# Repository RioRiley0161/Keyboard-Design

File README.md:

# Keyboard-Design
Custom keyboard design 
NEW FILES WONT UPLOAD SO I CREATED A NEW REVISED 60% FOR MY BASE 
----------------------------
Check out updated version at https://github.com/RioRiley0161/Keyboard-PCB

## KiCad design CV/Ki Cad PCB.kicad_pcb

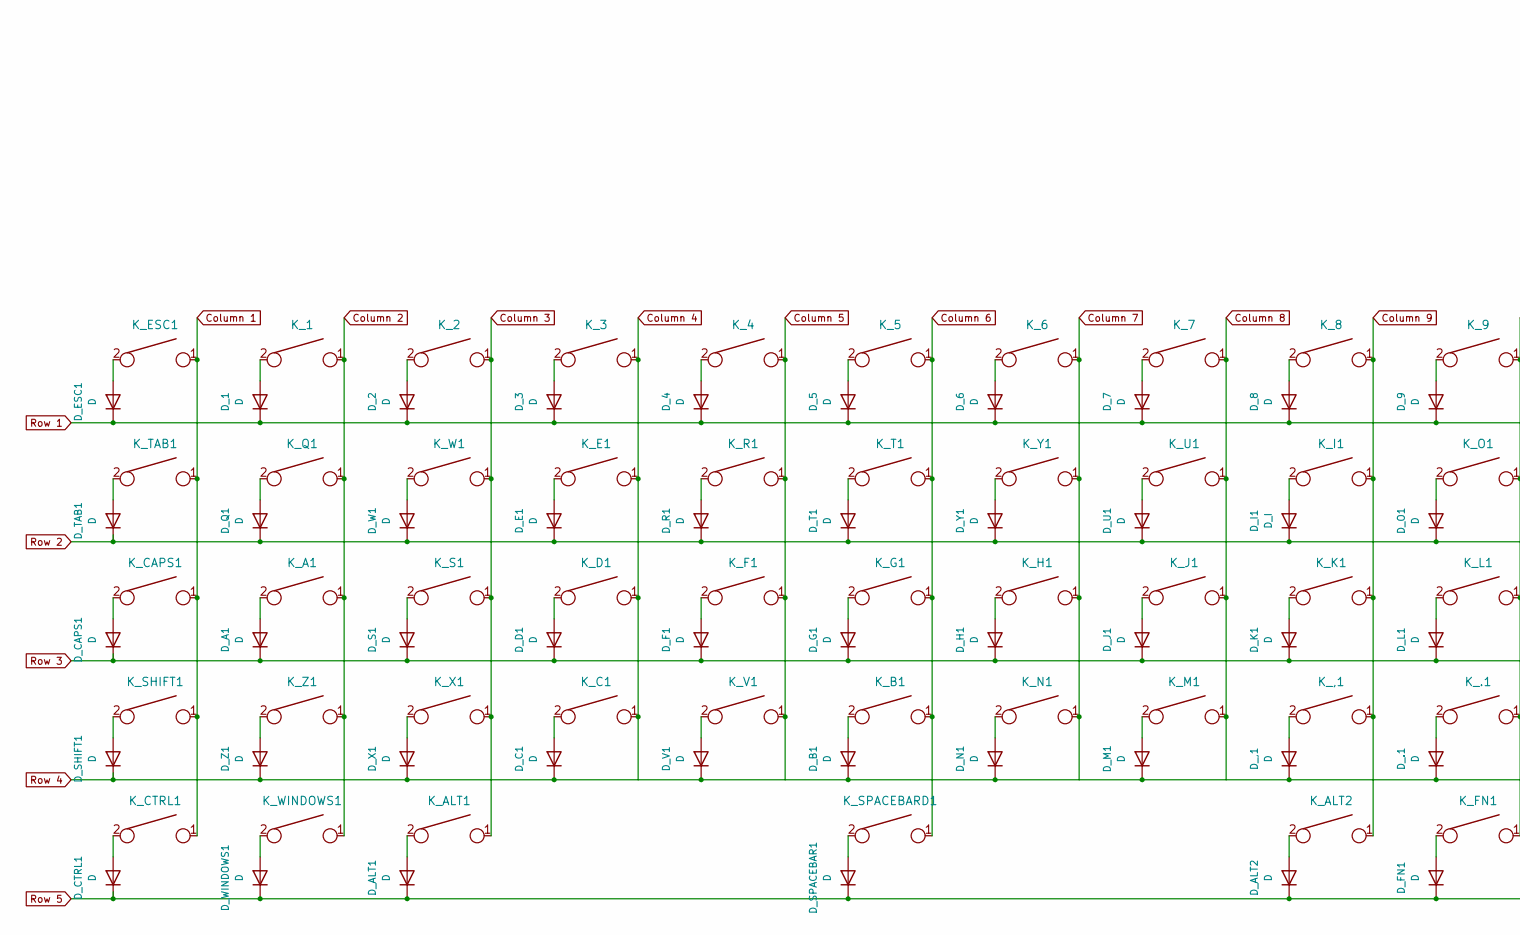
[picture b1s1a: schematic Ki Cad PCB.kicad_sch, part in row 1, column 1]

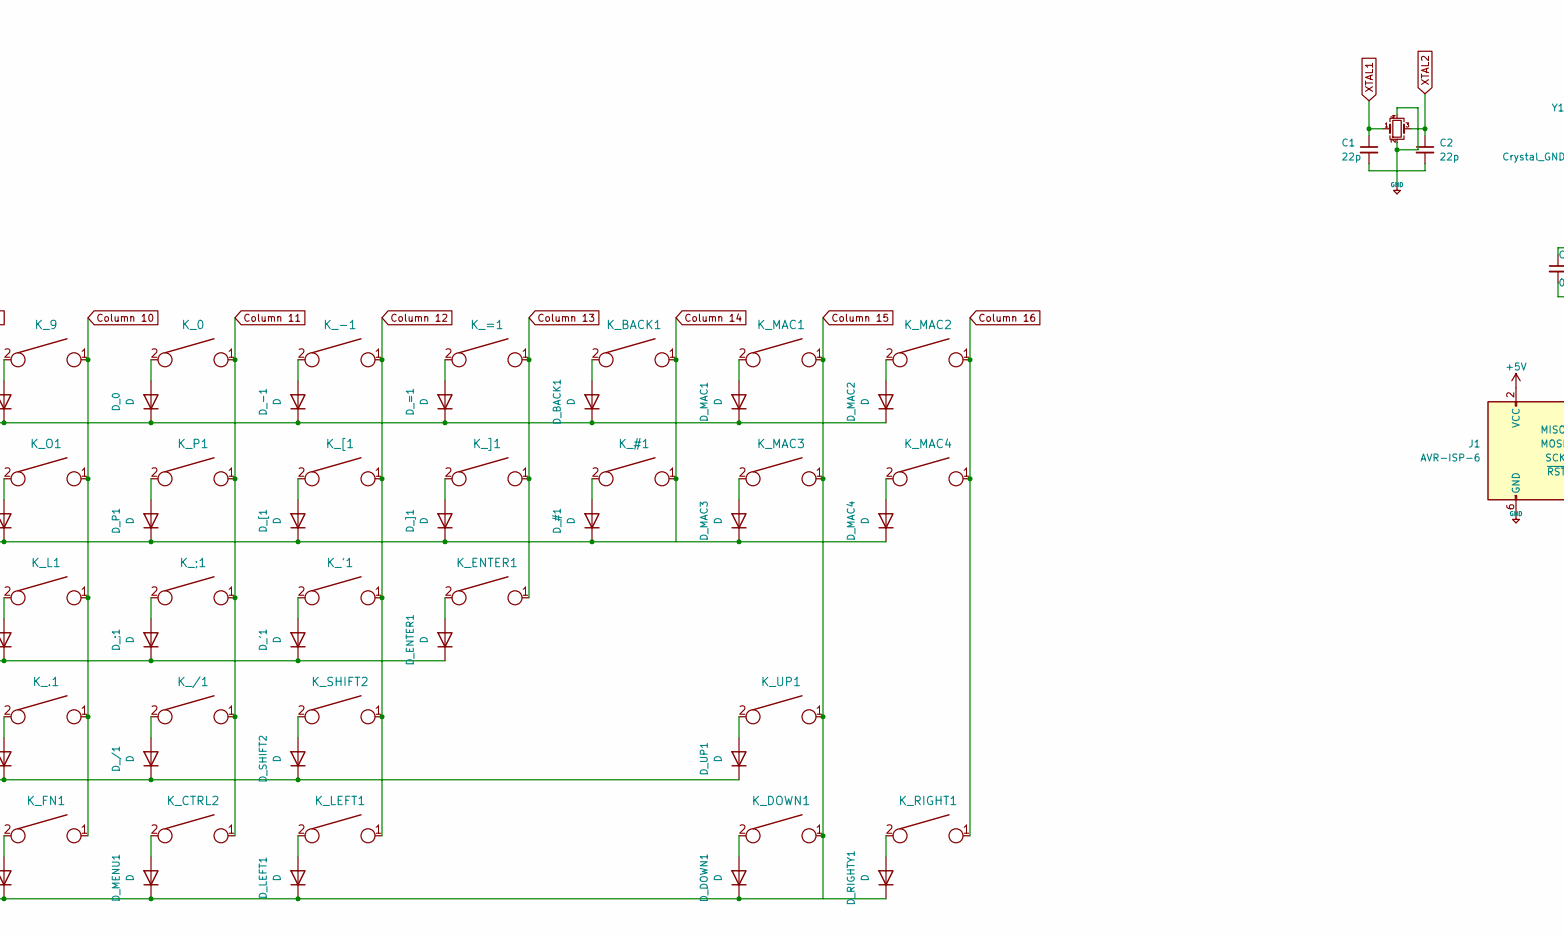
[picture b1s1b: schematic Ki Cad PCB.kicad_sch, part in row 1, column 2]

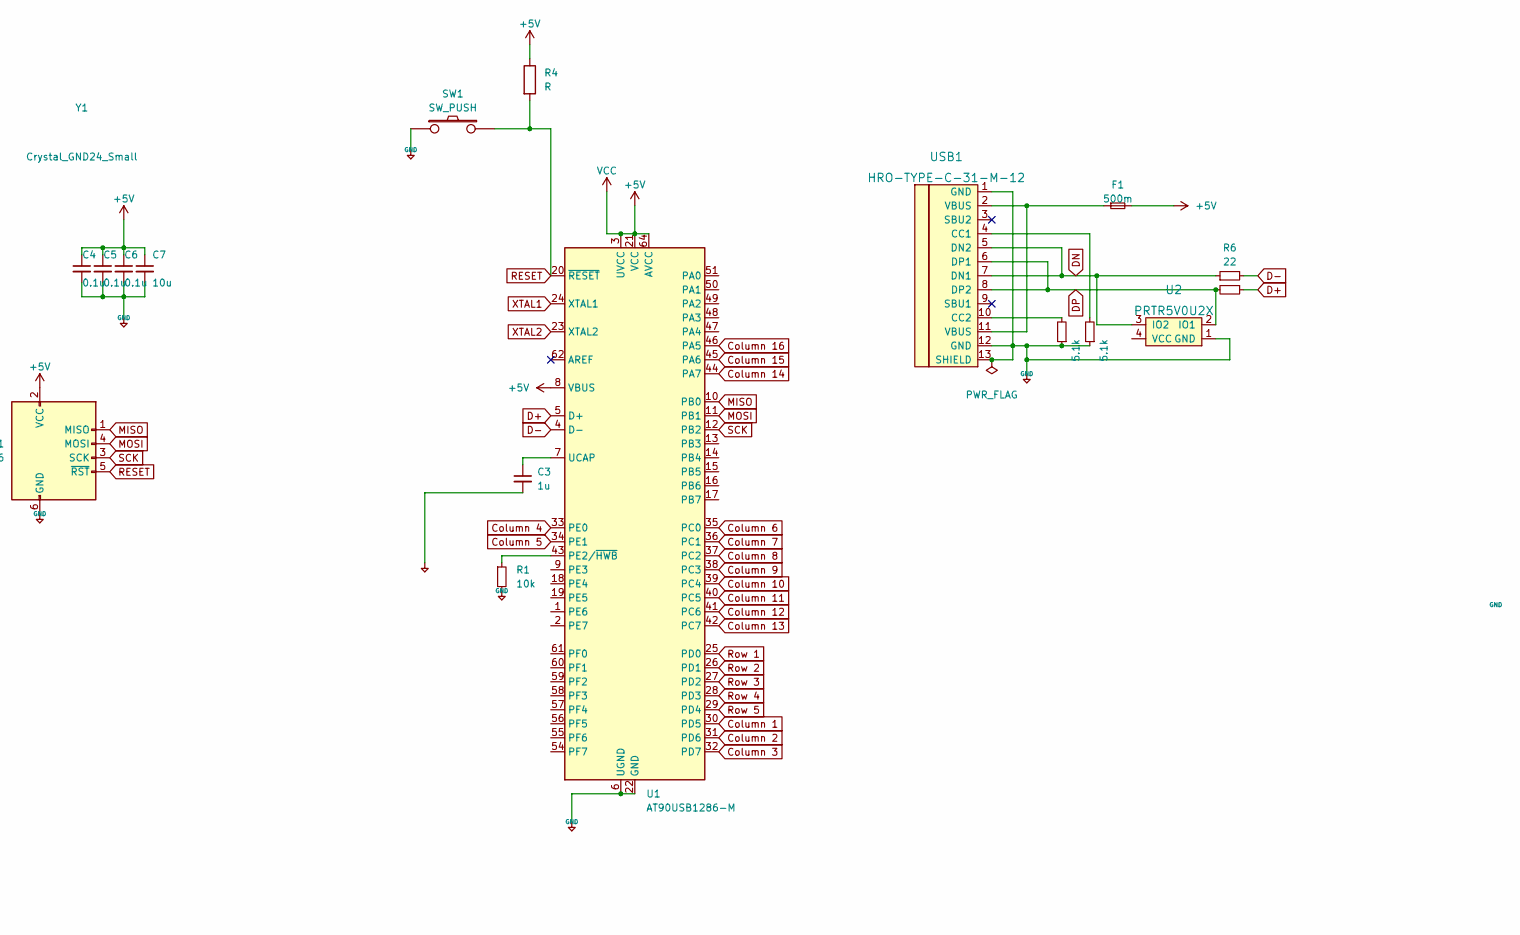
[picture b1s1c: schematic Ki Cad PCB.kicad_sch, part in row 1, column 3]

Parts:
C1, C2: 22p; C_0805_2012Metric
C3: 1u; C_0805_2012Metric
C4, C5, C6: 0.1u; C_0805_2012Metric
C7: 10u; C_0805_2012Metric
D_0, D_1, D_2, D_3, D_4, D_5, D_6, D_7, D_8, D_9, D_.1: D; D_SOD123_axial
D_#1: D; D_SOD123_axial
D_'1: D; D_SOD123_axial
D_,1: D; D_SOD123_axial
D_-1: D; D_SOD123_axial
D_/1: D; D_SOD123_axial
D_;1: D; D_SOD123_axial
D_=1: D; D_SOD123_axial
D_A1: D; D_SOD123_axial
D_ALT1, D_ALT2: D; D_SOD123_axial
D_B1: D; D_SOD123_axial
D_BACK1: D; D_SOD123_axial
D_C1: D; D_SOD123_axial
D_CAPS1: D; D_SOD123_axial
D_CTRL1: D; D_SOD123_axial
D_D1: D; D_SOD123_axial
D_DOWN1: D; D_SOD123_axial
D_E1: D; D_SOD123_axial
D_ENTER1: D; D_SOD123_axial
D_ESC1: D; D_SOD123_axial
D_F1: D; D_SOD123_axial
D_FN1: D; D_SOD123_axial
D_G1: D; D_SOD123_axial
D_H1: D; D_SOD123_axial
D_I1: D_I; D_SOD123_axial
D_J1: D; D_SOD123_axial
D_K1: D; D_SOD123_axial
D_L1: D; D_SOD123_axial
D_LEFT1: D; D_SOD123_axial
D_M1: D; D_SOD123_axial
D_MAC1, D_MAC2, D_MAC3, D_MAC4: D; D_SOD123_axial
D_MENU1: D; D_SOD123_axial
D_N1: D; D_SOD123_axial
D_O1: D; D_SOD123_axial
D_P1: D; D_SOD123_axial
D_Q1: D; D_SOD123_axial
D_R1: D; D_SOD123_axial
D_RIGHTY1: D; D_SOD123_axial
D_S1: D; D_SOD123_axial
D_SHIFT1, D_SHIFT2: D; D_SOD123_axial
D_SPACEBAR1: D; D_SOD123_axial
D_T1: D; D_SOD123_axial
D_TAB1: D; D_SOD123_axial
D_U1: D; D_SOD123_axial
D_UP1: D; D_SOD123_axial
D_V1: D; D_SOD123_axial
D_W1: D; D_SOD123_axial
D_WINDOWS1: D; D_SOD123_axial
D_X1: D; D_SOD123_axial
D_Y1: D; D_SOD123_axial
D_Z1: D; D_SOD123_axial
D_[1: D; D_SOD123_axial
D_]1: D; D_SOD123_axial
F1: 500m; Fuse_1206_3216Metric_Pad1.42x1.75mm_HandSolder
J1: AVR-ISP-6; Reset_Pretty-Mask
K_0, K_1, K_2, K_3, K_4, K_5, K_6, K_7, K_8, K_9, K_.1: KEYSW; SW_Cherry_MX_1.00u_Plate
K_#1: KEYSW; SW_Cherry_MX_1.50u_Plate
K_'1: KEYSW; SW_Cherry_MX_1.00u_Plate
K_,1: KEYSW; SW_Cherry_MX_1.00u_Plate
K_-1: KEYSW; SW_Cherry_MX_1.00u_Plate
K_/1: KEYSW; SW_Cherry_MX_1.00u_Plate
K_;1: KEYSW; SW_Cherry_MX_1.00u_Plate
K_=1: KEYSW; SW_Cherry_MX_1.00u_Plate
K_A1: KEYSW; SW_Cherry_MX_1.00u_Plate
K_ALT1, K_ALT2: KEYSW; SW_Cherry_MX_1.25u_Plate
K_B1: KEYSW; SW_Cherry_MX_1.00u_Plate
K_BACK1: KEYSW; SW_Cherry_MX_2.00u_Plate
K_C1: KEYSW; SW_Cherry_MX_1.00u_Plate
K_CAPS1: KEYSW; SW_Cherry_MX_1.75u_Plate
K_CTRL1, K_CTRL2: KEYSW; SW_Cherry_MX_1.25u_Plate
K_D1: KEYSW; SW_Cherry_MX_1.00u_Plate
K_DOWN1: KEYSW; SW_Cherry_MX_1.00u_Plate
K_E1: KEYSW; SW_Cherry_MX_1.00u_Plate
K_ENTER1: KEYSW; SW_Cherry_MX_2.25u_Plate
K_ESC1: KEYSW; SW_Cherry_MX_1.00u_Plate
K_F1: KEYSW; SW_Cherry_MX_1.00u_Plate
K_FN1: KEYSW; SW_Cherry_MX_1.25u_Plate
K_G1: KEYSW; SW_Cherry_MX_1.00u_Plate
K_H1: KEYSW; SW_Cherry_MX_1.00u_Plate
K_I1: KEYSW; SW_Cherry_MX_1.00u_Plate
K_J1: KEYSW; SW_Cherry_MX_1.00u_Plate
K_K1: KEYSW; SW_Cherry_MX_1.00u_Plate
K_L1: KEYSW; SW_Cherry_MX_1.00u_Plate
K_LEFT1: KEYSW; SW_Cherry_MX_1.00u_Plate
K_M1: KEYSW; SW_Cherry_MX_1.00u_Plate
K_MAC1, K_MAC2, K_MAC3, K_MAC4: KEYSW; SW_Cherry_MX_1.00u_Plate
K_N1: KEYSW; SW_Cherry_MX_1.00u_Plate
K_O1: KEYSW; SW_Cherry_MX_1.00u_Plate
K_P1: KEYSW; SW_Cherry_MX_1.00u_Plate
K_Q1: KEYSW; SW_Cherry_MX_1.00u_Plate
K_R1: KEYSW; SW_Cherry_MX_1.00u_Plate
K_RIGHT1: KEYSW; SW_Cherry_MX_1.00u_Plate
K_S1: KEYSW; SW_Cherry_MX_1.00u_Plate
K_SHIFT1: KEYSW; SW_Cherry_MX_2.25u_Plate
K_SHIFT2: KEYSW; SW_Cherry_MX_2.75u_Plate
K_SPACEBARD1: KEYSW; SW_Cherry_MX_6.25u_Plate
K_T1: KEYSW; SW_Cherry_MX_1.00u_PCB
K_TAB1: KEYSW; SW_Cherry_MX_1.50u_Plate
K_U1: KEYSW; SW_Cherry_MX_1.00u_Plate
K_UP1: KEYSW; SW_Cherry_MX_1.00u_Plate
K_V1: KEYSW; SW_Cherry_MX_1.00u_Plate
K_W1: KEYSW; SW_Cherry_MX_1.00u_Plate
K_WINDOWS1: KEYSW; SW_Cherry_MX_1.25u_Plate
K_X1: KEYSW; SW_Cherry_MX_1.00u_Plate
K_Y1: KEYSW; SW_Cherry_MX_1.00u_Plate
K_Z1: KEYSW; SW_Cherry_MX_1.00u_Plate
K_[1: KEYSW; SW_Cherry_MX_1.00u_Plate
K_]1: KEYSW; SW_Cherry_MX_1.00u_Plate
R1: 10k; R_0805_2012Metric
R2, R3: 5.1k; R_0805_2012Metric
R4: R; R_0805_2012Metric
R6, R7: 22; R_0805_2012Metric
SW1: SW_PUSH; SW_SPST_SKQG_WithStem
U1: AT90USB1286-M; QFN-64-1EP_9x9mm_P0.5mm_EP7.5x7.5mm
U2: PRTR5V0U2X; SOT143B
USB1: HRO-TYPE-C-31-M-12; HRO-TYPE-C-31-M-12-HandSoldering
Y1: Crystal_GND24_Small; Crystal_SMD_3225-4Pin_3.2x2.5mm

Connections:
Column 1: K_CAPS1.1, K_CTRL1.1, K_ESC1.1, K_SHIFT1.1, K_TAB1.1, U1.30 (PD5)
Column 2: K_1.1, K_A1.1, K_Q1.1, K_WINDOWS1.1, K_Z1.1, U1.31 (PD6)
Column 3: K_2.1, K_ALT1.1, K_S1.1, K_W1.1, K_X1.1, U1.32 (PD7)
Column 4: K_3.1, K_C1.1, K_D1.1, K_E1.1, U1.33 (PE0)
Column 5: K_4.1, K_F1.1, K_R1.1, K_V1.1, U1.34 (PE1)
Column 6: K_5.1, K_B1.1, K_G1.1, K_SPACEBARD1.1, K_T1.1, U1.35 (PC0)
Column 7: K_6.1, K_H1.1, K_N1.1, K_Y1.1, U1.36 (PC1)
Column 8: K_7.1, K_J1.1, K_M1.1, K_U1.1, U1.37 (PC2)
Column 9: K_8.1, K_,1.1, K_ALT2.1, K_I1.1, K_K1.1, U1.38 (PC3)
Column 10: K_9.1, K_.1.1, K_FN1.1, K_L1.1, K_O1.1, U1.39 (PC4)
Column 11: K_0.1, K_/1.1, K_;1.1, K_CTRL2.1, K_P1.1, U1.40 (PC5)
Column 12: K_'1.1, K_-1.1, K_LEFT1.1, K_SHIFT2.1, K_[1.1, U1.41 (PC6)
Column 13: K_=1.1, K_ENTER1.1, K_]1.1, U1.42 (PC7)
Column 14: K_#1.1, K_BACK1.1, U1.44 (PA7)
Column 15: K_DOWN1.1, K_MAC1.1, K_MAC3.1, K_UP1.1, U1.45 (PA6)
Column 16: K_MAC2.1, K_MAC4.1, K_RIGHT1.1, U1.46 (PA5)
D+: R7.1, U1.5 (D+)
D-: R6.2, U1.4 (D-)
DN: R6.1, U2.3 (IO2), USB1.5 (DN2), USB1.7 (DN1)
DP: R7.2, U2.2 (IO1), USB1.6 (DP1), USB1.8 (DP2)
MISO: J1.1 (MISO), U1.10 (PB0)
MOSI: J1.4 (MOSI), U1.11 (PB1)
unnamed: C1.2, C2.2
unnamed: C3.1, U1.7 (UCAP)
unnamed: D_0.2 (A), K_0.2
unnamed: D_1.2 (A), K_1.2
unnamed: D_2.2 (A), K_2.2
unnamed: D_3.2 (A), K_3.2
unnamed: D_4.2 (A), K_4.2
unnamed: D_5.2 (A), K_5.2
unnamed: D_6.2 (A), K_6.2
unnamed: D_7.2 (A), K_7.2
unnamed: D_8.2 (A), K_8.2
unnamed: D_9.2 (A), K_9.2
unnamed: D_#1.2 (A), K_#1.2
unnamed: D_'1.2 (A), K_'1.2
unnamed: D_,1.2 (A), K_,1.2
unnamed: D_-1.2 (A), K_-1.2
unnamed: D_.1.2 (A), K_.1.2
unnamed: D_/1.2 (A), K_/1.2
unnamed: D_;1.2 (A), K_;1.2
unnamed: D_=1.2 (A), K_=1.2
unnamed: D_A1.2 (A), K_A1.2
unnamed: D_ALT1.2 (A), K_ALT1.2
unnamed: D_ALT2.2 (A), K_ALT2.2
unnamed: D_B1.2 (A), K_B1.2
unnamed: D_BACK1.2 (A), K_BACK1.2
unnamed: D_C1.2 (A), K_C1.2
unnamed: D_CAPS1.2 (A), K_CAPS1.2
unnamed: D_CTRL1.2 (A), K_CTRL1.2
unnamed: D_D1.2 (A), K_D1.2
unnamed: D_DOWN1.2 (A), K_DOWN1.2
unnamed: D_E1.2 (A), K_E1.2
unnamed: D_ENTER1.2 (A), K_ENTER1.2
unnamed: D_ESC1.2 (A), K_ESC1.2
unnamed: D_F1.2 (A), K_F1.2
unnamed: D_FN1.2 (A), K_FN1.2
unnamed: D_G1.2 (A), K_G1.2
unnamed: D_H1.2 (A), K_H1.2
unnamed: D_I1.2 (A), K_I1.2
unnamed: D_J1.2 (A), K_J1.2
unnamed: D_K1.2 (A), K_K1.2
unnamed: D_L1.2 (A), K_L1.2
unnamed: D_LEFT1.2 (A), K_LEFT1.2
unnamed: D_M1.2 (A), K_M1.2
unnamed: D_MAC1.2 (A), K_MAC1.2
unnamed: D_MAC2.2 (A), K_MAC2.2
unnamed: D_MAC3.2 (A), K_MAC3.2
unnamed: D_MAC4.2 (A), K_MAC4.2
unnamed: D_MENU1.2 (A), K_CTRL2.2
unnamed: D_N1.2 (A), K_N1.2
unnamed: D_O1.2 (A), K_O1.2
unnamed: D_P1.2 (A), K_P1.2
unnamed: D_Q1.2 (A), K_Q1.2
unnamed: D_R1.2 (A), K_R1.2
unnamed: D_RIGHTY1.2 (A), K_RIGHT1.2
unnamed: D_S1.2 (A), K_S1.2
unnamed: D_SHIFT1.2 (A), K_SHIFT1.2
unnamed: D_SHIFT2.2 (A), K_SHIFT2.2
unnamed: D_SPACEBAR1.2 (A), K_SPACEBARD1.2
unnamed: D_T1.2 (A), K_T1.2
unnamed: D_TAB1.2 (A), K_TAB1.2
unnamed: D_U1.2 (A), K_U1.2
unnamed: D_UP1.2 (A), K_UP1.2
unnamed: D_V1.2 (A), K_V1.2
unnamed: D_W1.2 (A), K_W1.2
unnamed: D_WINDOWS1.2 (A), K_WINDOWS1.2
unnamed: D_X1.2 (A), K_X1.2
unnamed: D_Y1.2 (A), K_Y1.2
unnamed: D_Z1.2 (A), K_Z1.2
unnamed: D_[1.2 (A), K_[1.2
unnamed: D_]1.2 (A), K_]1.2
unnamed: R1.1, U1.43 (PE2/~HWB)
unnamed: R3.2, USB1.4 (CC1)
unnamed: R2.2, USB1.10 (CC2)
unnamed: F1.1, USB1.2 (VBUS), USB1.11 (VBUS)
RESET: J1.5 (~RST), R4.2, SW1.2, U1.20 (~RESET)
Row 1: D_0.1 (K), D_1.1 (K), D_2.1 (K), D_3.1 (K), D_4.1 (K), D_5.1 (K), D_6.1 (K), D_7.1 (K), D_8.1 (K), D_9.1 (K), D_-1.1 (K), D_=1.1 (K), D_BACK1.1 (K), D_ESC1.1 (K), D_MAC1.1 (K), D_MAC2.1 (K), U1.25 (PD0)
Row 2: D_#1.1 (K), D_E1.1 (K), D_I1.1 (K), D_MAC3.1 (K), D_MAC4.1 (K), D_O1.1 (K), D_P1.1 (K), D_Q1.1 (K), D_R1.1 (K), D_T1.1 (K), D_TAB1.1 (K), D_U1.1 (K), D_W1.1 (K), D_Y1.1 (K), D_[1.1 (K), D_]1.1 (K), U1.26 (PD1)
Row 3: D_'1.1 (K), D_;1.1 (K), D_A1.1 (K), D_CAPS1.1 (K), D_D1.1 (K), D_ENTER1.1 (K), D_F1.1 (K), D_G1.1 (K), D_H1.1 (K), D_J1.1 (K), D_K1.1 (K), D_L1.1 (K), D_S1.1 (K), U1.27 (PD2)
Row 4: D_,1.1 (K), D_.1.1 (K), D_/1.1 (K), D_B1.1 (K), D_C1.1 (K), D_M1.1 (K), D_N1.1 (K), D_SHIFT1.1 (K), D_SHIFT2.1 (K), D_UP1.1 (K), D_V1.1 (K), D_X1.1 (K), D_Z1.1 (K), U1.28 (PD3)
Row 5: D_ALT1.1 (K), D_ALT2.1 (K), D_CTRL1.1 (K), D_DOWN1.1 (K), D_FN1.1 (K), D_LEFT1.1 (K), D_MENU1.1 (K), D_RIGHTY1.1 (K), D_SPACEBAR1.1 (K), D_WINDOWS1.1 (K), U1.29 (PD4)
SCK: J1.3 (SCK), U1.12 (PB2)
XTAL1: C1.1, U1.24 (XTAL1), Y1.1
XTAL2: C2.1, U1.23 (XTAL2), Y1.3

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
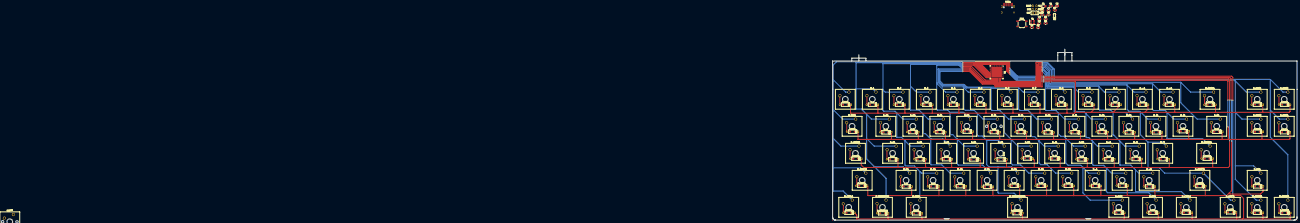
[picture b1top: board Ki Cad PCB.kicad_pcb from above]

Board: 2 copper layers, 327.6 x 120.6 mm, 156 parts (0 on the bottom side), 106 nets.

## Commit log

2022-01-18 KL
    Keyboard layout for initial design.
2022-01-18 Keyboard Layout
    New drawing of keyboard layout for PCB
2022-01-18 Backplate
    Updated Backplate design
2022-01-18 BackPlate
2022-01-18 Backplate Done
    Backplate for keyboard is finished for the final product.
2022-01-20 PCB Schematic
2022-01-20 Ki Cad Schematic for PCB
2022-01-22 New Backplate Rendition
    New Backplate Design to allow for diode usage at the top of the keyboard instead of on the switch
2022-01-22 Schematic Transfer
    Shematic Transfer to pcb editor and all switches allocated to the right place with correct placement
2022-01-27 Schematics Change
    Wired all the microcontroller in schematics. Added Clock, Power Decoupler, ISP header, Reset switch, USB C connector
2022-01-27 Updated pcb
    Added all the traces for the pcb on while referring back to our switch matrix.
2022-01-27 Rename Backplating.dxf to CV/Backplating.dxf
2022-01-27 Rename BACKPLATE END STAGE.dxf to First Renditions/BACKPLATE END STAGE.dxf
2022-01-27 Rename Drawing Of KLE.dxf to First Renditions/Drawing Of KLE.dxf
2022-01-27 Rename Ki Cad PCB.kicad_sch to CV/Ki Cad PCB.kicad_sch
2022-01-27 Rename Ki Cad PCB.kicad_pcb to CV/Ki Cad PCB.kicad_pcb
2022-01-27 Rename New Drawing.dxf to First Renditions/New Drawing.dxf
